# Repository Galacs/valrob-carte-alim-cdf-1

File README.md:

# Carte alim CDF 1

ESP32-S3-WROOM-1 5v 10A and 12v 10A six efuse protected with current and state monitoring channels power supply boards

The repo also contains minimal firmware for the ESP32 MCU.

## IC List

- ESP32-S3-WROOM-1 (Main MCU Module)
- TLV757P (MCU 3v3 LDO)
- 2X TPS56A37 (10A smps)
- SN65HVD (CAN transceiver)
- 7x TPS259472 (5A efuse)

## Top preview

## Preview 3d render

## Pictures

## Pin definitions

```c
#define PWR_STATUS_PIN 17

#define PG_12V_PIN 37
#define PG_5V_PIN 48
#define VSENSE_PIN 17

#define CAN_RX 35
#define CAN_TX 36

#define BAU 42

#define ILM_5V_1_PIN 1
#define ILM_5V_2_PIN 3
#define ILM_5V_3_PIN 2

#define ILM_12V_1_PIN 1
#define ILM_12V_2_PIN 7
#define ILM_12V_3_PIN 5
#define ILM_12V_4_PIN 4

#define EN_5V_1_PIN 39
#define EN_5V_2_PIN 21
#define EN_5V_3_PIN 40

#define EN_12V_1_PIN 11
#define EN_12V_2_PIN 13
#define EN_12V_3_PIN 8

#define PG_5V_1_PIN 38
#define PG_5V_2_PIN 47
#define PG_5V_3_PIN 41

#define PG_12V_1_PIN 10
#define PG_12V_2_PIN 12
#define PG_12V_3_PIN 18
#define PG_12V_4_PIN 16
```

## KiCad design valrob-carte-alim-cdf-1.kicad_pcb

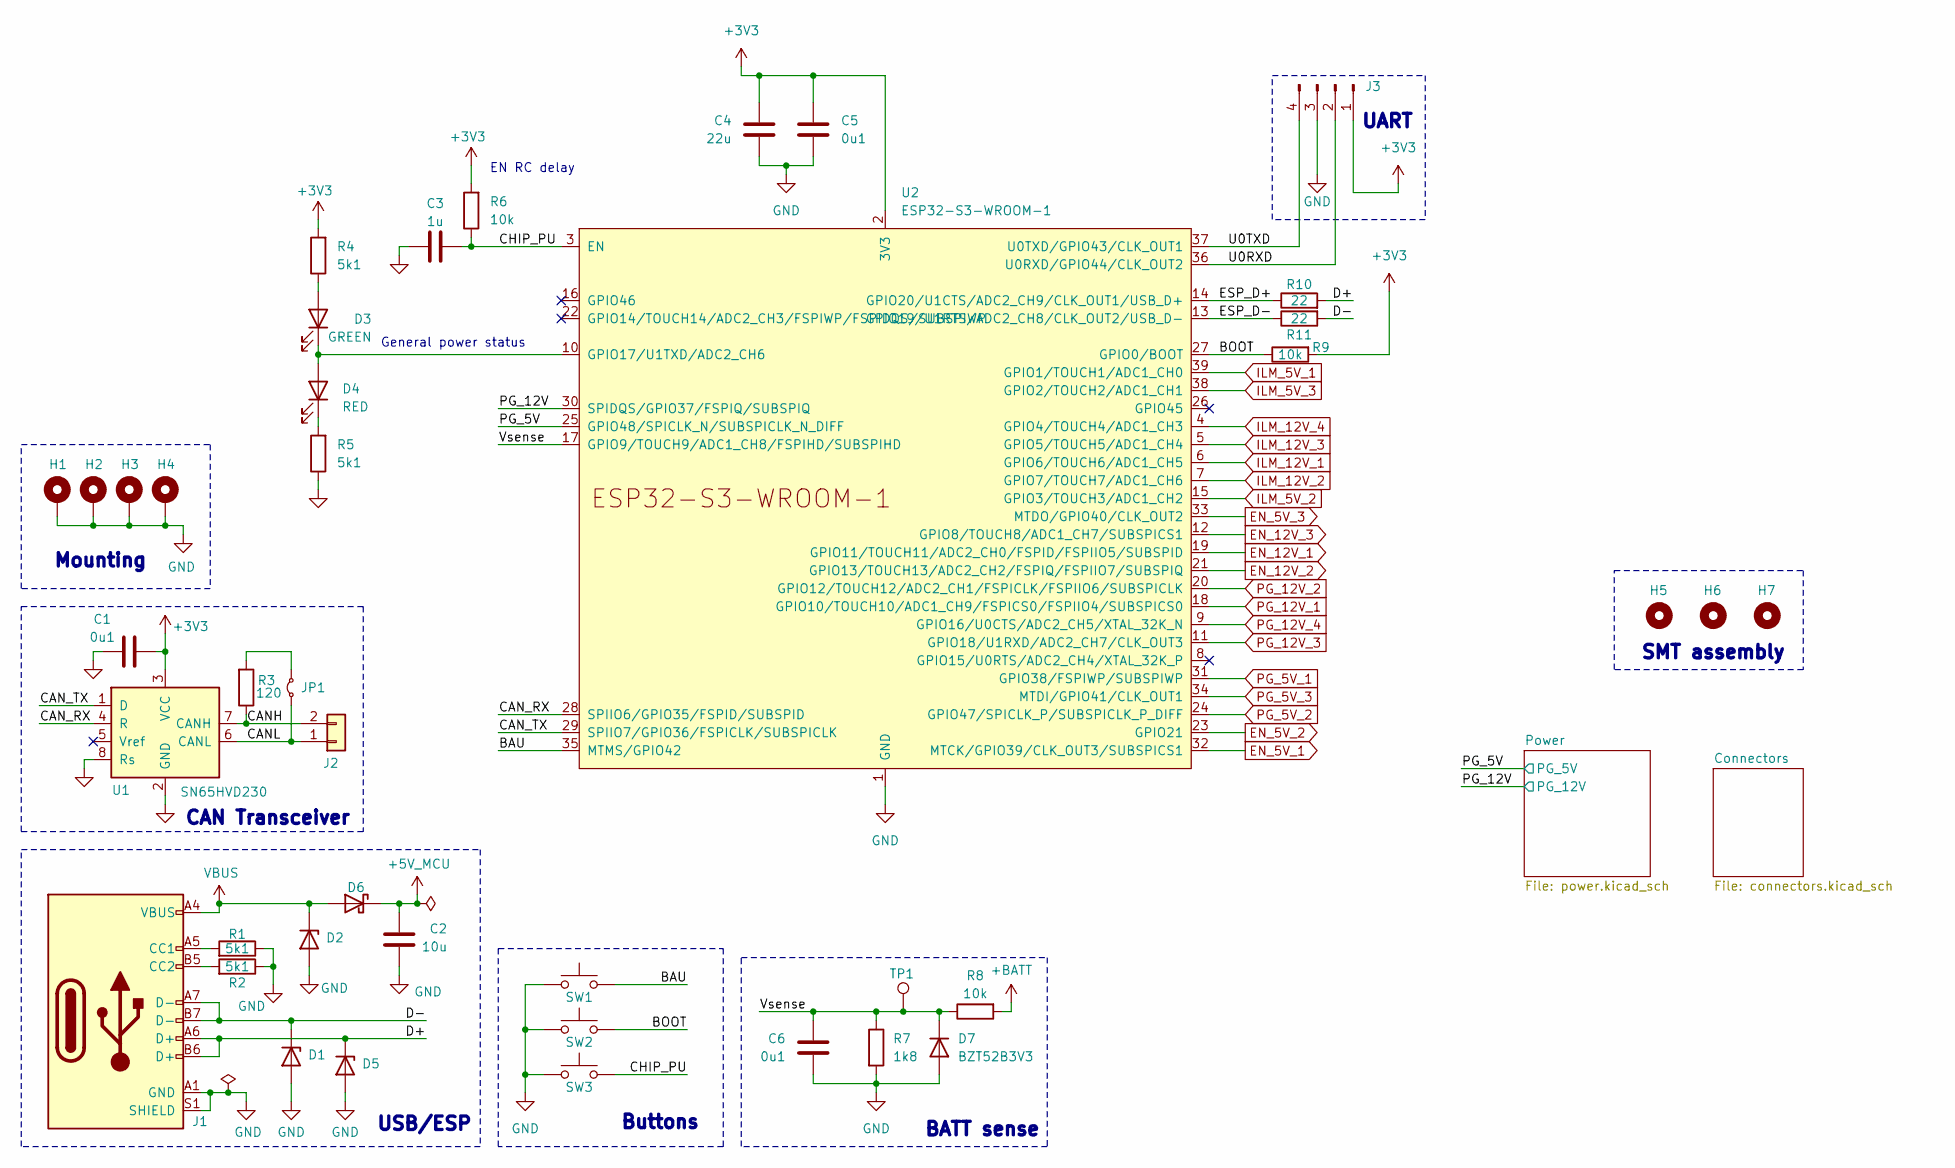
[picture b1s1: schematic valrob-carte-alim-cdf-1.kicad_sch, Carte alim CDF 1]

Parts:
C1, C5, C6: 0u1; C_0402_1005Metric; Manufacturer Part Number CL05B104KB54PNC; JLCPCB Part # C307331
C2: 10u; C_0603_1608Metric; Manufacturer Part Number CL10A106KP8NNNC; JLCPCB Part # C19702
C3: 1u; C_0402_1005Metric; Manufacturer Part Number CL05A105KA5NQNC; JLCPCB Part # C52923
C4: 22u; C_0603_1608Metric; Manufacturer Part Number CL10A226MQ8NRNC; JLCPCB Part # C59461
D1, D2, D5: H5VU10U; Diode_DFN1006; Manufacturer Part Number H5VU10U; JLCPCB Part # C22395519
D3: GREEN; LED_0805_2012Metric; Manufacturer Part Number KT-0805G; JLCPCB Part # C2297
D4: RED; LED_0603_1608Metric; Manufacturer Part Number KT-0603R; JLCPCB Part # C2286
D6: D_Schottky; D_SMA; Manufacturer Part Number SS54; JLCPCB Part # C22452
D7: BZT52B3V3; D_SOD-123; Manufacturer Part Number BZT52B3V3; JLCPCB Part # C19077392
H1, H2, H3, H4: MountingHole_Pad; MountingHole_2.2mm_M2_Pad_Via
H5, H6, H7: MountingHole; ToolingHole_1.152mm
J1: USB_C_Receptacle_USB2.0_14P; USB_C_Receptacle_HRO_TYPE-C-31-M-12; Manufacturer Part Number TYPE-C16PIN; JLCPCB Part # C393939
J2: Conn_01x02; JST_XH_B2B-XH-A_1x02_P2.50mm_Vertical; Manufacturer Part Number B2B-XH-A(LF)(SN); JLCPCB Part # C158012
J3: Conn_01x04_Pin; PinHeader_1x04_P2.54mm_Vertical
JP1: Jumper_2_Small_Bridged; SolderJumper-2_P1.3mm_Open_RoundedPad1.0x1.5mm
R1, R2, R4, R5: 5k1; R_0402_1005Metric; Manufacturer Part Number 0402WGF5101TCE; JLCPCB Part # C25905
R3: 120; R_1206_3216Metric; Manufacturer Part Number 1206W4F1200T5E; JLCPCB Part # C17909
R6, R8, R9: 10k; R_0402_1005Metric; Manufacturer Part Number 0402WGF1002TCE; JLCPCB Part # C25744
R7: 1k8; R_0603_1608Metric; Manufacturer Part Number 0603WAF1801T5E; JLCPCB Part # C4177
R10, R11: 22; R_0402_1005Metric; Manufacturer Part Number 0402WGF220JTCE; JLCPCB Part # C25092
SW1: SW_Push; JST_XH_B2B-XH-A_1x02_P2.50mm_Vertical; Manufacturer Part Number B2B-XH-A(LF)(SN); JLCPCB Part # C158012
SW2, SW3: SW_Push; SW_SPST_TS-1088-xR020; Manufacturer Part Number TS-1088-AR02016; JLCPCB Part # C720477
TP1: TestPoint; TestPoint_Pad_D2.0mm
U1: SN65HVD230; SOIC-8_3.9x4.9mm_P1.27mm; Manufacturer Part Number SN65HVD230DR; JLCPCB Part # C12084
U2: ESP32-S3-WROOM-1; Manufacturer Part Number ESP32-S3-WROOM-1-N8R2; JLCPCB Part # C2913204

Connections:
+3V3: C1.1, C4.1, C5.1, J3.1, R4.2, R6.2, R9.2, U1.3 (VCC), U2.2 (3V3); also elsewhere on the board
+5V_MCU: C2.1, D6.1 (K); also elsewhere on the board
+BATT: R8.2; also elsewhere on the board
/BAU: SW1.2, U2.35 (MTMS/GPIO42)
/BOOT: R9.1, SW2.2, U2.27 (GPIO0/BOOT)
/CANH: J2.2, R3.1, U1.7 (CANH)
/CANL: J2.1, JP1.1 (A), U1.6 (CANL)
/CAN_RX: U1.4 (R), U2.28 (SPIIO6/GPIO35/FSPID/SUBSPID)
/CAN_TX: U1.1 (D), U2.29 (SPIIO7/GPIO36/FSPICLK/SUBSPICLK)
/CHIP_PU: C3.2, R6.1, SW3.2, U2.3 (EN)
/D+: D5.1 (K), J1.A6 (D+), J1.B6 (D+), R10.2
/D-: D1.1 (K), J1.A7 (D-), J1.B7 (D-), R11.2
/ESP_D+: R10.1, U2.14 (GPIO20/U1CTS/ADC2_CH9/CLK_OUT1/USB_D+)
/ESP_D-: R11.1, U2.13 (GPIO19/U1RTS/ADC2_CH8/CLK_OUT2/USB_D-)
/PG_5V: U2.25 (GPIO48/SPICLK_N/SUBSPICLK_N_DIFF); also elsewhere on the board
/PG_12V: U2.30 (SPIDQS/GPIO37/FSPIQ/SUBSPIQ); also elsewhere on the board
/U0RXD: J3.2, U2.36 (U0RXD/GPIO44/CLK_OUT2)
/U0TXD: J3.4, U2.37 (U0TXD/GPIO43/CLK_OUT1)
/Vsense: C6.1, D7.1 (K), R7.1, R8.1, TP1.1, U2.17 (GPIO9/TOUCH9/ADC1_CH8/FSPIHD/SUBSPIHD)
EN_5V_1: U2.32 (MTCK/GPIO39/CLK_OUT3/SUBSPICS1); also elsewhere on the board
EN_5V_2: U2.23 (GPIO21); also elsewhere on the board
EN_5V_3: U2.33 (MTDO/GPIO40/CLK_OUT2); also elsewhere on the board
EN_12V_1: U2.19 (GPIO11/TOUCH11/ADC2_CH0/FSPID/FSPIIO5/S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); also elsewhere on the board
EN_12V_2: U2.21 (GPIO13/TOUCH13/ADC2_CH2/FSPIQ/FSPIIO7/S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); also elsewhere on the board
EN_12V_3: U2.12 (GPIO8/TOUCH8/ADC1_CH7/SUBSPICS1); also elsewhere on the board
GND: C1.2, C2.2, C3.1, C4.2, C5.2, C6.2, D1.2 (A), D2.2 (A), D5.2 (A), D7.2 (A), H1.1, H2.1, H3.1, H4.1, J1.A1 (GND), J1.A12 (GND), J1.B1 (GND), J1.B12 (GND), J1.S1 (SHIELD), J3.3, R1.1, R2.1, R5.1, R7.2, SW1.1, SW2.1, SW3.1, U1.2 (GND), U1.8 (Rs), U2.1 (GND), U2.40 (GND), U2.41 (GND); also elsewhere on the board
ILM_5V_1: U2.39 (GPIO1/TOUCH1/ADC1_CH0); also elsewhere on the board
ILM_5V_2: U2.15 (GPIO3/TOUCH3/ADC1_CH2); also elsewhere on the board
ILM_5V_3: U2.38 (GPIO2/TOUCH2/ADC1_CH1); also elsewhere on the board
ILM_12V_1: U2.6 (GPIO6/TOUCH6/ADC1_CH5); also elsewhere on the board
ILM_12V_2: U2.7 (GPIO7/TOUCH7/ADC1_CH6); also elsewhere on the board
ILM_12V_3: U2.5 (GPIO5/TOUCH5/ADC1_CH4); also elsewhere on the board
ILM_12V_4: U2.4 (GPIO4/TOUCH4/ADC1_CH3); also elsewhere on the board
unnamed: D3.2 (A), R4.1
unnamed: D3.1 (K), D4.2 (A), U2.10 (GPIO17/U1TXD/ADC2_CH6)
unnamed: D4.1 (K), R5.2
unnamed: J1.A5 (CC1), R1.2
unnamed: J1.B5 (CC2), R2.2
unnamed: JP1.2 (B), R3.2
PG_5V_1: U2.31 (GPIO38/FSPIWP/SUBSPIWP); also elsewhere on the board
PG_5V_2: U2.24 (GPIO47/SPICLK_P/SUBSPICLK_P_DIFF); also elsewhere on the board
PG_5V_3: U2.34 (MTDI/GPIO41/CLK_OUT1); also elsewhere on the board
PG_12V_1: U2.18 (GPIO10/TOUCH10/ADC1_CH9/FSPICS0/FSPIIO4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); also elsewhere on the board
PG_12V_2: U2.20 (GPIO12/TOUCH12/ADC2_CH1/FSPICLK/FSPIIO6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); also elsewhere on the board
PG_12V_3: U2.11 (GPIO18/U1RXD/ADC2_CH7/CLK_OUT3); also elsewhere on the board
PG_12V_4: U2.9 (GPIO16/U0CTS/ADC2_CH5/XTAL_32K_N); also elsewhere on the board
VBUS: D2.1 (K), D6.2 (A), J1.A4 (VBUS), J1.A9 (VBUS), J1.B4 (VBUS), J1.B9 (VBUS)

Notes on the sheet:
EN RC delay
Mounting
SMT assembly
UART
Buttons
USB/ESP
BATT sense
CAN Transceiver
General power status

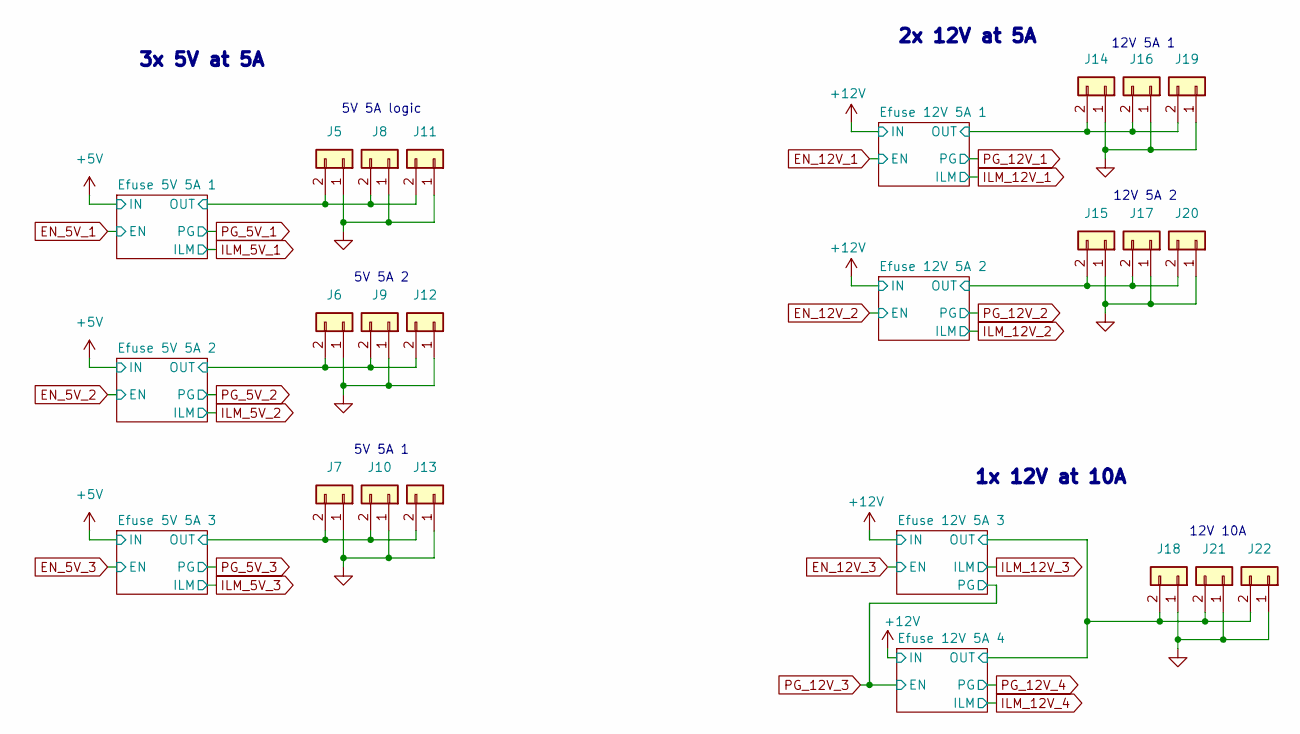
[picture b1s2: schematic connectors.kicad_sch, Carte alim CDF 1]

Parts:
J5, J6, J7, J8, J9, J10, J11, J12, J13, J14, J15, J16, J17, J18, J19, J20, J21, J22: Conn_01x02; JST_XH_B2B-XH-A_1x02_P2.50mm_Vertical; Manufacturer Part Number B2B-XH-A(LF)(SN); JLCPCB Part # C158012

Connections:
/Connectors/Efuse 5V 5A 1/OUT: J5.2, J8.2, J11.2; also elsewhere on the board
/Connectors/Efuse 5V 5A 2/OUT: J6.2, J9.2, J12.2; also elsewhere on the board
/Connectors/Efuse 5V 5A 3/OUT: J7.2, J10.2, J13.2; also elsewhere on the board
/Connectors/Efuse 12V 5A 1/OUT: J14.2, J16.2, J19.2; also elsewhere on the board
/Connectors/Efuse 12V 5A 2/OUT: J15.2, J17.2, J20.2; also elsewhere on the board
/Connectors/Efuse 12V 5A 3/OUT: J18.2, J21.2, J22.2; also elsewhere on the board
GND: J5.1, J6.1, J7.1, J8.1, J9.1, J10.1, J11.1, J12.1, J13.1, J14.1, J15.1, J16.1, J17.1, J18.1, J19.1, J20.1, J21.1, J22.1; also elsewhere on the board

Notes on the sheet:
5V 5A 1
12V 5A 2
12V 5A 1
2x 12V at 5A
1x 12V at 10A
12V 10A
5V 5A 2
3x 5V at 5A
5V 5A logic

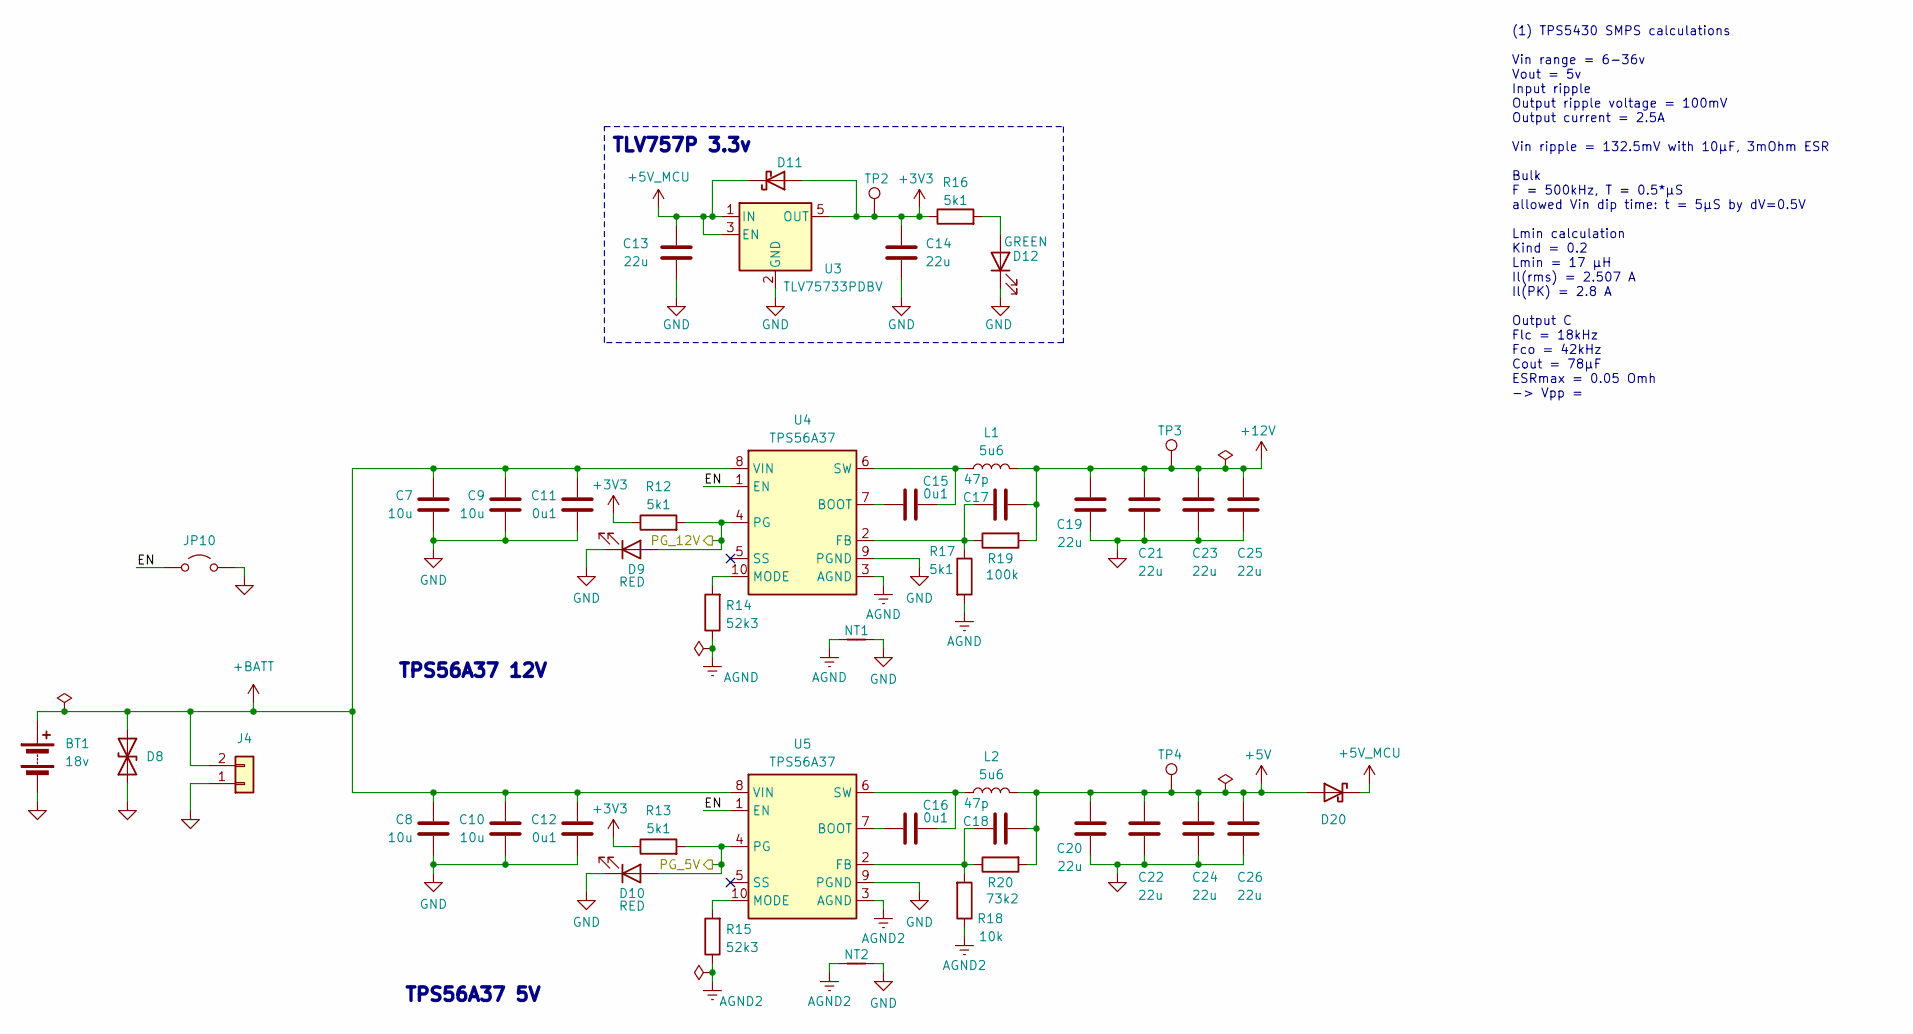
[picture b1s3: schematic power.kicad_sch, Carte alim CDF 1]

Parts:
BT1: 18v; Power battery holder
C7, C8, C9, C10: 10u; C_0805_2012Metric; Manufacturer Part Number GRM21BR61H106KE43L; JLCPCB Part # C440198
C11, C12, C15, C16: 0u1; C_0402_1005Metric; Manufacturer Part Number CL05B104KB54PNC; JLCPCB Part # C307331
C13, C14: 22u; C_0603_1608Metric; Manufacturer Part Number CL10A226MQ8NRNC; JLCPCB Part # C59461
C17, C18: 47p; C_0402_1005Metric; Manufacturer Part Number 0402CG470J500NT; JLCPCB Part # C1567
C19, C20, C21, C22, C23, C24, C25, C26: 22u; C_0805_2012Metric; Manufacturer Part Number CL21A226MAQNNNE; JLCPCB Part # C45783
D8: D_TVS; D_SMA; Manufacturer Part Number SMAJ33CA; JLCPCB Part # C19077549
D9, D10: RED; LED_0603_1608Metric; Manufacturer Part Number KT-0603R; JLCPCB Part # C2286
D11, D20: D_Schottky; D_SMA; Manufacturer Part Number SS54; JLCPCB Part # C22452
D12: GREEN; LED_0805_2012Metric; Manufacturer Part Number KT-0805G; JLCPCB Part # C2297
J4: Conn_01x02; JST_XH_B2B-XH-A_1x02_P2.50mm_Vertical; Manufacturer Part Number B2B-XH-A(LF)(SN); JLCPCB Part # C158012
JP10: Jumper_2_Small_Open; PinHeader_2x01_P2.54mm_Vertical
L1, L2: 5u6; L_Bourns_SRP1050WA; Manufacturer Part Number SMMS1050-5R6M; JLCPCB Part # C149541
NT1, NT2: NetTie_2; NetTie-2_SMD_Pad0.5mm
R12, R13, R16, R17: 5k1; R_0402_1005Metric; Manufacturer Part Number 0402WGF5101TCE; JLCPCB Part # C25905
R14, R15: 52k3; R_0402_1005Metric; Manufacturer Part Number 0402WGF5232TCE; JLCPCB Part # C26982
R18: 10k; R_0402_1005Metric; Manufacturer Part Number 0402WGF1002TCE; JLCPCB Part # C25744
R19: 100k; R_0402_1005Metric; Manufacturer Part Number 0402WGF1003TCE; JLCPCB Part # C25741
R20: 73k2; R_0402_1005Metric; Manufacturer Part Number 0402WGF7322TCE; JLCPCB Part # C26986
TP2, TP3, TP4: TestPoint; TestPoint_Pad_D2.0mm
U3: TLV75733PDBV; SOT-23-5; Manufacturer Part Number TLV75733PDBVR; JLCPCB Part # C485517
U4, U5: TPS56A37; Texas_RPA0010A_VQFN-HR-10_3x3mm_P0.5mm; Manufacturer Part Number TPS56A37RPAR; JLCPCB Part # C22392669

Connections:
+3V3: C14.2, D11.2 (A), R12.1, R13.1, R16.1, TP2.1, U3.5 (OUT); also elsewhere on the board
+5V: C18.2, C20.1, C22.1, C24.1, C26.1, D20.2 (A), L2.2, R20.2, TP4.1; also elsewhere on the board
+5V_MCU: C13.2, D11.1 (K), D20.1 (K), U3.1 (IN), U3.3 (EN); also elsewhere on the board
+12V: C17.2, C19.1, C21.1, C23.1, C25.1, L1.2, R19.2, TP3.1; also elsewhere on the board
+BATT: BT1.1 (+), C7.1, C8.1, C9.1, C10.1, C11.1, C12.1, D8.2 (A2), J4.2, U4.8 (VIN), U5.8 (VIN); also elsewhere on the board
/PG_5V: D10.2 (A), R13.2, U5.4 (PG); also elsewhere on the board
/PG_12V: D9.2 (A), R12.2, U4.4 (PG); also elsewhere on the board
/Power/EN: JP10.1 (A), U4.1 (EN), U5.1 (EN)
AGND: NT1.1, R14.1, R17.2, U4.3 (AGND)
AGND2: NT2.1, R15.1, R18.1, U5.3 (AGND)
GND: BT1.2 (-), C7.2, C8.2, C9.2, C10.2, C11.2, C12.2, C13.1, C14.1, C19.2, C20.2, C21.2, C22.2, C23.2, C24.2, C25.2, C26.2, D8.1 (A1), D9.1 (K), D10.1 (K), D12.1 (K), J4.1, JP10.2 (B), NT1.2, NT2.2, U3.2 (GND), U4.9 (PGND), U5.9 (PGND); also elsewhere on the board
unnamed: D12.2 (A), R16.2
unnamed: C15.1, U4.7 (BOOT)
unnamed: C17.1, R17.1, R19.1, U4.2 (FB)
unnamed: R14.2, U4.10 (MODE)
unnamed: C15.2, L1.1, U4.6 (SW)
unnamed: C16.1, U5.7 (BOOT)
unnamed: C18.1, R18.2, R20.1, U5.2 (FB)
unnamed: R15.2, U5.10 (MODE)
unnamed: C16.2, L2.1, U5.6 (SW)

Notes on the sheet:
TPS56A37 12V
TLV757P 3.3v
TPS56A37 5V
(1) TPS5430 SMPS calculations Vin range = 6-36v Vout = 5v Input ripple Output ripple voltage = 100mV Output current = 2.5A Vin ripple = 132.5mV with 10µF, 3mOhm ESR Bulk F = 500kHz, T = 0.5*µS allowed Vin dip time: t = 5µS by dV=0.5V Lmin calculation Kind = 0.2 Lmin = 17 µH Il(rms) = 2.507 A Il(PK)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

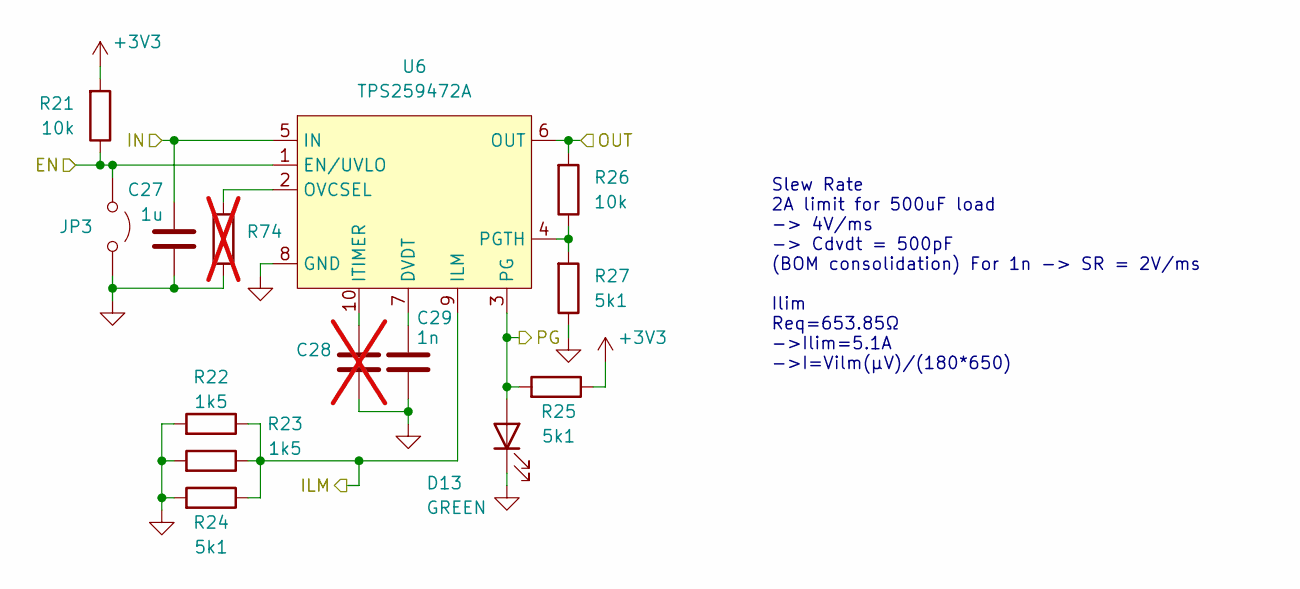
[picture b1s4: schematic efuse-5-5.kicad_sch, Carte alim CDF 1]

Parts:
C27: 1u; C_0402_1005Metric; Manufacturer Part Number CL05A105KA5NQNC; JLCPCB Part # C52923
C28: C; C_0402_1005Metric; not fitted
C29: 1n; C_0402_1005Metric; Manufacturer Part Number 0402B102K500NT; JLCPCB Part # C1523
D13: GREEN; LED_0805_2012Metric; Manufacturer Part Number KT-0805G; JLCPCB Part # C2297
JP3: Jumper_2_Small_Open; PinHeader_2x01_P2.54mm_Vertical
R21, R26: 10k; R_0402_1005Metric; Manufacturer Part Number 0402WGF1002TCE; JLCPCB Part # C25744
R22, R23: 1k5; R_0402_1005Metric; Manufacturer Part Number 0402WGF1501TCE; JLCPCB Part # C25867
R24, R25, R27: 5k1; R_0402_1005Metric; Manufacturer Part Number 0402WGF5101TCE; JLCPCB Part # C25905
R74: R; R_0402_1005Metric; not fitted
U6: TPS259472A; Texas_RPW0010A_VQFN-HR-10_2x2mm_P0.5mm; Manufacturer Part Number TPS259472ARPWR; JLCPCB Part # C3662789

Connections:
+3V3: R21.2, R25.1; also elsewhere on the board
+5V: C27.2, U6.5 (IN); also elsewhere on the board
/Connectors/Efuse 5V 5A 1/OUT: R26.2, U6.6 (OUT); also elsewhere on the board
EN_5V_1: JP3.1 (A), R21.1, U6.1 (EN/UVLO); also elsewhere on the board
GND: C27.1, C28.2, C29.2, D13.1 (K), JP3.2 (B), R22.2, R23.2, R24.2, R27.1, R74.2, U6.8 (GND); also elsewhere on the board
ILM_5V_1: R22.1, R23.1, R24.1, U6.9 (ILM); also elsewhere on the board
unnamed: C29.1, U6.7 (DVDT)
unnamed: C28.1, U6.10 (ITIMER)
unnamed: R74.1, U6.2 (OVCSEL)
unnamed: R26.1, R27.2, U6.4 (PGTH)
PG_5V_1: D13.2 (A), R25.2, U6.3 (PG); also elsewhere on the board

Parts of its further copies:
C30, C45: 1u; C_0402_1005Metric; Manufacturer Part Number CL05A105KA5NQNC; JLCPCB Part # C52923
C31, C46: C; C_0402_1005Metric; not fitted
C32, C47: 1n; C_0402_1005Metric; Manufacturer Part Number 0402B102K500NT; JLCPCB Part # C1523
D14, D19: GREEN; LED_0805_2012Metric; Manufacturer Part Number KT-0805G; JLCPCB Part # C2297
JP4, JP9: Jumper_2_Small_Open; PinHeader_2x01_P2.54mm_Vertical
R28, R33, R67, R72: 10k; R_0402_1005Metric; Manufacturer Part Number 0402WGF1002TCE; JLCPCB Part # C25744
R29, R30, R68, R69: 1k5; R_0402_1005Metric; Manufacturer Part Number 0402WGF1501TCE; JLCPCB Part # C25867
R31, R32, R34, R70, R71, R73: 5k1; R_0402_1005Metric; Manufacturer Part Number 0402WGF5101TCE; JLCPCB Part # C25905
R75, R76: R; R_0402_1005Metric; not fitted
U7, U12: TPS259472A; Texas_RPW0010A_VQFN-HR-10_2x2mm_P0.5mm; Manufacturer Part Number TPS259472ARPWR; JLCPCB Part # C3662789

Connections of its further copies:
+3V3: R28.2, R32.1, R67.2, R71.1; also elsewhere on the board
+5V: C30.2, C45.2, U7.5 (IN), U12.5 (IN); also elsewhere on the board
/Connectors/Efuse 5V 5A 2/OUT: R72.2, U12.6 (OUT); also elsewhere on the board
/Connectors/Efuse 5V 5A 3/OUT: R33.2, U7.6 (OUT); also elsewhere on the board
EN_5V_2: JP9.1 (A), R67.1, U12.1 (EN/UVLO); also elsewhere on the board
EN_5V_3: JP4.1 (A), R28.1, U7.1 (EN/UVLO); also elsewhere on the board
GND: C30.1, C31.2, C32.2, C45.1, C46.2, C47.2, D14.1 (K), D19.1 (K), JP4.2 (B), JP9.2 (B), R29.2, R30.2, R31.2, R34.1, R68.2, R69.2, R70.2, R73.1, R75.2, R76.2, U7.8 (GND), U12.8 (GND); also elsewhere on the board
ILM_5V_2: R68.1, R69.1, R70.1, U12.9 (ILM); also elsewhere on the board
ILM_5V_3: R29.1, R30.1, R31.1, U7.9 (ILM); also elsewhere on the board
unnamed: C32.1, U7.7 (DVDT)
unnamed: C31.1, U7.10 (ITIMER)
unnamed: R75.1, U7.2 (OVCSEL)
unnamed: R33.1, R34.2, U7.4 (PGTH)
unnamed: C47.1, U12.7 (DVDT)
unnamed: C46.1, U12.10 (ITIMER)
unnamed: R76.1, U12.2 (OVCSEL)
unnamed: R72.1, R73.2, U12.4 (PGTH)
PG_5V_2: D19.2 (A), R71.2, U12.3 (PG); also elsewhere on the board
PG_5V_3: D14.2 (A), R32.2, U7.3 (PG); also elsewhere on the board

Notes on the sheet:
Slew Rate 2A limit for 500uF load -> 4V/ms -> Cdvdt = 500pF (BOM consolidation) For 1n -> SR = 2V/ms Ilim Req=653.85Ω ->Ilim=5.1A ->I=Vilm(µV)/(180*650)

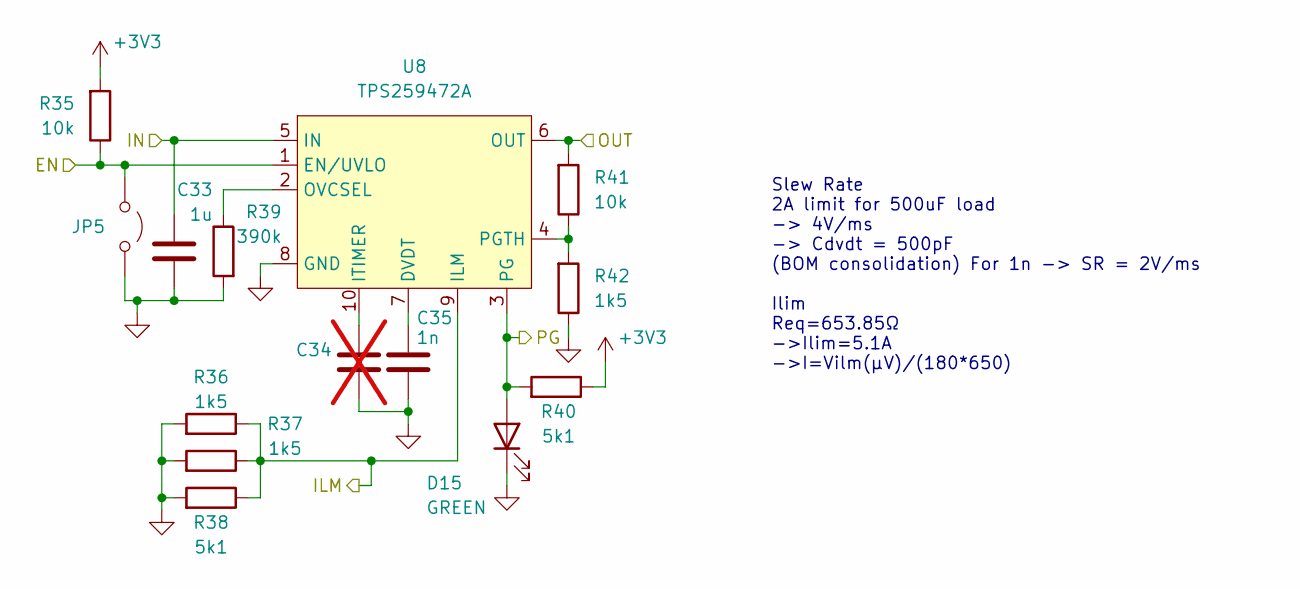
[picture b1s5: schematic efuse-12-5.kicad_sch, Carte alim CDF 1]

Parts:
C33: 1u; C_0402_1005Metric; Manufacturer Part Number CL05A105KA5NQNC; JLCPCB Part # C52923
C34: C; C_0402_1005Metric; not fitted
C35: 1n; C_0402_1005Metric; Manufacturer Part Number 0402B102K500NT; JLCPCB Part # C1523
D15: GREEN; LED_0805_2012Metric; Manufacturer Part Number KT-0805G; JLCPCB Part # C2297
JP5: Jumper_2_Small_Open; PinHeader_2x01_P2.54mm_Vertical
R35, R41: 10k; R_0402_1005Metric; Manufacturer Part Number 0402WGF1002TCE; JLCPCB Part # C25744
R36, R37, R42: 1k5; R_0402_1005Metric; Manufacturer Part Number 0402WGF1501TCE; JLCPCB Part # C25867
R38, R40: 5k1; R_0402_1005Metric; Manufacturer Part Number 0402WGF5101TCE; JLCPCB Part # C25905
R39: 390k; R_0402_1005Metric; Manufacturer Part Number 0402WGF3903TCE; JLCPCB Part # C25782
U8: TPS259472A; Texas_RPW0010A_VQFN-HR-10_2x2mm_P0.5mm; Manufacturer Part Number TPS259472ARPWR; JLCPCB Part # C3662789

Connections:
+3V3: R35.2, R40.1; also elsewhere on the board
+12V: C33.2, U8.5 (IN); also elsewhere on the board
/Connectors/Efuse 12V 5A 1/OUT: R41.2, U8.6 (OUT); also elsewhere on the board
EN_12V_1: JP5.1 (A), R35.1, U8.1 (EN/UVLO); also elsewhere on the board
GND: C33.1, C34.2, C35.2, D15.1 (K), JP5.2 (B), R36.2, R37.2, R38.2, R39.2, R42.1, U8.8 (GND); also elsewhere on the board
ILM_12V_1: R36.1, R37.1, R38.1, U8.9 (ILM); also elsewhere on the board
unnamed: C35.1, U8.7 (DVDT)
unnamed: C34.1, U8.10 (ITIMER)
unnamed: R39.1, U8.2 (OVCSEL)
unnamed: R41.1, R42.2, U8.4 (PGTH)
PG_12V_1: D15.2 (A), R40.2, U8.3 (PG); also elsewhere on the board

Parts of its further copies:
C36, C39, C42: 1u; C_0402_1005Metric; Manufacturer Part Number CL05A105KA5NQNC; JLCPCB Part # C52923
C37, C40, C43: C; C_0402_1005Metric; not fitted
C38, C41, C44: 1n; C_0402_1005Metric; Manufacturer Part Number 0402B102K500NT; JLCPCB Part # C1523
D16, D17, D18: GREEN; LED_0805_2012Metric; Manufacturer Part Number KT-0805G; JLCPCB Part # C2297
JP6, JP7, JP8: Jumper_2_Small_Open; PinHeader_2x01_P2.54mm_Vertical
R43, R49, R51, R57, R59, R65: 10k; R_0402_1005Metric; Manufacturer Part Number 0402WGF1002TCE; JLCPCB Part # C25744
R44, R45, R50, R52, R53, R58, R60, R61, R66: 1k5; R_0402_1005Metric; Manufacturer Part Number 0402WGF1501TCE; JLCPCB Part # C25867
R46, R48, R54, R56, R62, R64: 5k1; R_0402_1005Metric; Manufacturer Part Number 0402WGF5101TCE; JLCPCB Part # C25905
R47, R55, R63: 390k; R_0402_1005Metric; Manufacturer Part Number 0402WGF3903TCE; JLCPCB Part # C25782
U9, U10, U11: TPS259472A; Texas_RPW0010A_VQFN-HR-10_2x2mm_P0.5mm; Manufacturer Part Number TPS259472ARPWR; JLCPCB Part # C3662789

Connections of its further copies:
+3V3: R43.2, R48.1, R51.2, R56.1, R59.2, R64.1; also elsewhere on the board
+12V: C36.2, C39.2, C42.2, U9.5 (IN), U10.5 (IN), U11.5 (IN); also elsewhere on the board
/Connectors/Efuse 12V 5A 2/OUT: R49.2, U9.6 (OUT); also elsewhere on the board
/Connectors/Efuse 12V 5A 3/OUT: R57.2, R65.2, U10.6 (OUT), U11.6 (OUT); also elsewhere on the board
EN_12V_2: JP6.1 (A), R43.1, U9.1 (EN/UVLO); also elsewhere on the board
EN_12V_3: JP7.1 (A), R51.1, U10.1 (EN/UVLO); also elsewhere on the board
GND: C36.1, C37.2, C38.2, C39.1, C40.2, C41.2, C42.1, C43.2, C44.2, D16.1 (K), D17.1 (K), D18.1 (K), JP6.2 (B), JP7.2 (B), JP8.2 (B), R44.2, R45.2, R46.2, R47.2, R50.1, R52.2, R53.2, R54.2, R55.2, R58.1, R60.2, R61.2, R62.2, R63.2, R66.1, U9.8 (GND), U10.8 (GND), U11.8 (GND); also elsewhere on the board
ILM_12V_2: R44.1, R45.1, R46.1, U9.9 (ILM); also elsewhere on the board
ILM_12V_3: R52.1, R53.1, R54.1, U10.9 (ILM); also elsewhere on the board
ILM_12V_4: R60.1, R61.1, R62.1, U11.9 (ILM); also elsewhere on the board
unnamed: C38.1, U9.7 (DVDT)
unnamed: C37.1, U9.10 (ITIMER)
unnamed: R47.1, U9.2 (OVCSEL)
unnamed: R49.1, R50.2, U9.4 (PGTH)
unnamed: C41.1, U10.7 (DVDT)
unnamed: C40.1, U10.10 (ITIMER)
unnamed: R55.1, U10.2 (OVCSEL)
unnamed: R57.1, R58.2, U10.4 (PGTH)
unnamed: C44.1, U11.7 (DVDT)
unnamed: C43.1, U11.10 (ITIMER)
unnamed: R63.1, U11.2 (OVCSEL)
unnamed: R65.1, R66.2, U11.4 (PGTH)
PG_12V_2: D16.2 (A), R48.2, U9.3 (PG); also elsewhere on the board
PG_12V_3: D17.2 (A), JP8.1 (A), R56.2, R59.1, U10.3 (PG), U11.1 (EN/UVLO); also elsewhere on the board
PG_12V_4: D18.2 (A), R64.2, U11.3 (PG); also elsewhere on the board

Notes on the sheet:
Slew Rate 2A limit for 500uF load -> 4V/ms -> Cdvdt = 500pF (BOM consolidation) For 1n -> SR = 2V/ms Ilim Req=653.85Ω ->Ilim=5.1A ->I=Vilm(µV)/(180*650)

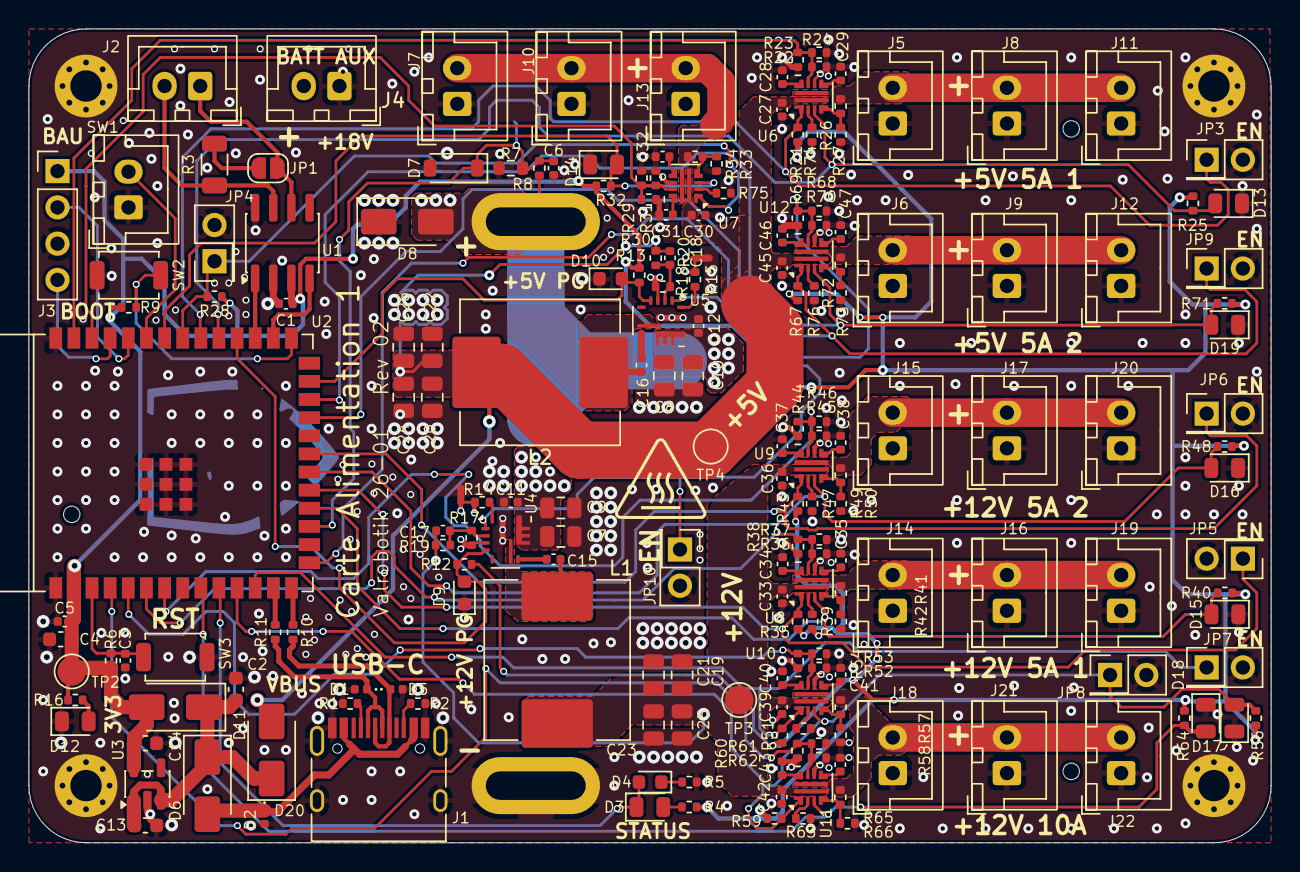
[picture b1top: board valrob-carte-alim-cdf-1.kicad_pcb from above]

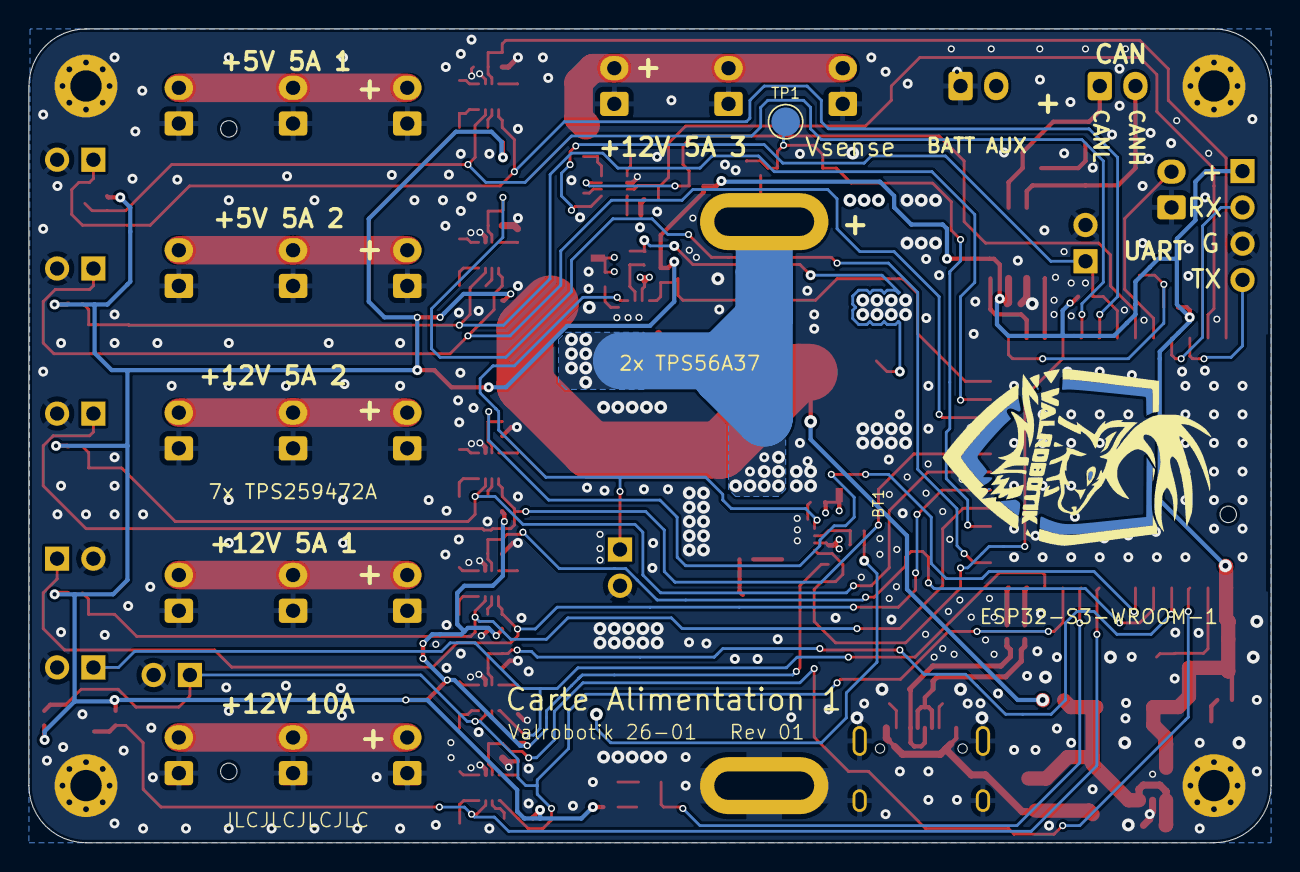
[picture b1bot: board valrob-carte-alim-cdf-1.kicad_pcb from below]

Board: 4 copper layers, 87.0 x 57.0 mm, 205 parts (2 on the bottom side), 95 nets.

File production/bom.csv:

Designator,Footprint,Quantity,Value,LCSC Part #
BT1,Power battery holder,1,18v,
"C1, C11, C12, C15, C16, C5, C6",0402,7,0u1,C307331
"C10, C7, C8, C9",0805,4,10u,C440198
"C13, C14, C4",0603,3,22u,C59461
"C17, C18",0402,2,47p,C1567
"C19, C20, C21, C22, C23, C24, C25, C26",0805,8,22u,C45783
C2,0603,1,10u,C19702
"C27, C3, C30, C33, C36, C39, C42, C45",0402,8,1u,C52923
"C29, C32, C35, C38, C41, C44, C47",0402,7,1n,C1523
"D1, D2, D5",Diode_DFN1006,3,H5VU10U,C22395519
"D10, D4, D9",0603,3,RED,C2286
"D11, D20, D6",D_SMA,3,D_Schottky,C22452
"D12, D13, D14, D15, D16, D17, D18, D19, D3",0805,9,GREEN,C2297
D7,D_SOD-123,1,BZT52B3V3,C19077392
D8,D_SMA,1,D_TVS,C19077549
J1,USB_C_Receptacle_HRO_TYPE-C-31-M-12,1,USB_C_Receptacle_USB2.0_14P,C393939
"J10, J11, J12, J13, J14, J15, J16, J17, J18, J19, J2, J20, J21, J22, J4, J5, J6, J7, J8, J9",JST_XH_B2B-XH-A_1x02_P2.50mm_Vertical,20,Conn_01x02,C158012
"JP10, JP3, JP4, JP5, JP6, JP7, JP8, JP9",PinHeader_2x01_P2.54mm_Vertical,8,Jumper_2_Small_Open,
"L1, L2",L_Bourns_SRP1050WA,2,5u6,C149541
"R1, R12, R13, R16, R17, R2, R24, R25, R27, R31, R32, R34, R38, R4, R40, R46, R48, R5, R54, R56, R62, R64, R70, R71, R73",0402,25,5k1,C25905
"R10, R11",0402,2,22,C25092
"R14, R15",0402,2,52k3,C26982
"R18, R21, R26, R28, R33, R35, R41, R43, R49, R51, R57, R59, R6, R65, R67, R72, R8, R9",0402,18,10k,C25744
R19,0402,1,100k,C25741
R20,0402,1,73k2,C26986
"R22, R23, R29, R30, R36, R37, R42, R44, R45, R50, R52, R53, R58, R60, R61, R66, R68, R69",0402,18,1k5,C25867
R3,1206,1,120,C17909
"R39, R47, R55, R63",0402,4,390k,C25782
R7,0603,1,1k8,C4177
SW1,JST_XH_B2B-XH-A_1x02_P2.50mm_Vertical,1,SW_Push,C158012
"SW2, SW3",SW_SPST_TS-1088-xR020,2,SW_Push,C720477
U1,SOIC-8_3.9x4.9mm_P1.27mm,1,SN65HVD230,C12084
"U10, U11, U12, U6, U7, U8, U9",Texas_RPW0010A_VQFN-HR-10_2x2mm_P0.5mm,7,TPS259472A,C3662789
U3,SOT-23-5,1,TLV75733PDBV,C485517
"U4, U5",Texas_RPA0010A_VQFN-HR-10_3x3mm_P0.5mm,2,TPS56A37,C22392669

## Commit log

2026-01-14 schem: add ESP32-S3-WROOM-1 MCU
2026-01-14 schem: add USBC connector
2026-01-14 schem: add TPS5430 5v logic SMPS
2026-01-14 schem: moved TSP5430 to power sheet
2026-01-14 schem: add efuse page
2026-01-14 schem: add BOOT and CHIP_PU btns
2026-01-14 schem: add TPS259472A efuse
2026-01-14 schem: add TPS56A37 12V SMPS
2026-01-14 schem: add TPS56A37 5V SMPS
2026-01-14 schem: add battery esd tvs diode
2026-01-14 schem: add TPS259472A 5V 5A efuse
2026-01-14 schem: add VBUS TO +5V jumper
2026-01-14 schem: add 2 5V rails
2026-01-14 schem: add 2 12V 5A rails
2026-01-14 schem: add ILM pins and 12V 10A rail
2026-01-14 schem: add TLV757P 3.3v LDO
2026-01-14 schem: reorganize connectors
2026-01-14 schem: add +BATT voltage sense
2026-01-14 schem: add CAN transceiver
2026-01-14 schem: add additional connector for batt vin
2026-01-14 schem: update 12v efuse net labels
2026-01-14 schem: add BAU
2026-01-14 schem: update 12V efuse component class
2026-01-15 schem: remove logic 5V smps
2026-01-15 schem: removed 5V output
2026-01-15 schem: add disable jumper to efuses
2026-01-15 schem: add esp32 gpio connections
2026-01-15 schem: add general power status leds
2026-01-15 schem: change aux batt power connector
2026-01-15 schem: add test points
2026-01-15 schem: run and fix ERC
2026-01-15 schem: add net classes
2026-01-15 schem: add battery holder footprint
2026-01-15 schem: update TPS259472A symbol
2026-01-15 schem: complete BOM
2026-01-15 schem: add sheet title
2026-01-15 schem: renumber
2026-01-15 pcb: import stackup and constraints
2026-01-15 pcb: import footprints from schema
2026-01-15 pcb: add missing 3D models
2026-01-15 pcb: add initial rough layout
2026-01-15 pcb: add battery step file
2026-01-16 schem: add mounting holes
2026-01-16 pcb: refine layout
2026-01-16 pcb: add smps layout
2026-01-16 pcb: add efuse layout
2026-01-16 pcb: finish initial layout
2026-01-16 pcb: line up 2.54 headers
2026-01-16 pcb: add can layout
2026-01-16 pcb: add gnd planes
2026-01-16 pcb: add grid/place origin
2026-01-16 pcb: add gnd vias
2026-01-16 pcb: add high I 12V and 5V pwr routing
2026-01-16 pcb: add 5V SMPS routing
2026-01-16 pcb: fix 12v copper pour appearance
2026-01-16 pcb: add 12V SMPS routing
2026-01-16 pcb: add usb routing
2026-01-16 pcb: add can routing
2026-01-16 pcb: complete smps routing
2026-01-16 pcb: add efuse 5v 3 routing
2026-01-16 pcb: add esp and ldo 3v3 routing
2026-01-16 schem: reorganize programmable gpios
2026-01-17 pcb: increase size of negative batt spokes
2026-01-17 pcb: add local efuse routing
2026-01-17 pcb: add CHIP_PU routing
2026-01-17 pcb: add efuses' PG leds and en jumpers routing
2026-01-17 pcb: add BAU routing
2026-01-17 schem: add general EN jumper
2026-01-17 pcb: add efuses' PG AND EN routing
2026-01-17 pcb: add vsense routing
2026-01-17 pcb: add efuses ILM routing
2026-01-17 pcb: add 5V SMPS PG routing
2026-01-17 pcb: add BOOT routing
2026-01-17 pcb: add missing efuse EN routing to MCU
2026-01-17 pcb: add 3V3 pwr routing
2026-01-17 pcb: run and fix DRC
2026-01-17 pcb: add stitching vias
2026-01-17 pcb: remove unused internal pads
2026-01-17 pcb(silkscreen): clean reference designators
2026-01-17 pcb: add title and logo
2026-01-17 pcb(silkscreen): add user txt
2026-01-17 pcb: add title
2026-01-21 schem/pcb: put vsense on adc input
2026-01-21 pcb: add production files
2026-01-21 schem/pcb: prevent TPS56A37 reverse current with new oringed 5v mcu rail
2026-01-21 pcb: switch smps power capacitors zone connection to solid
2026-01-21 regenerate production files
2026-01-21 pcb: clean silkscreen and regenerate production files
2026-02-08 fw: initial commit
2026-02-08 fw: add pins definitions
2026-02-08 fw: add power channel object
2026-02-08 fw: update platformio.ini
2026-02-08 fw: add power channel impl
2026-02-08 fw: add pwr led update fn
2026-02-08 fw: add ems update fn
2026-02-08 fw: fix channels ems states
2026-02-08 fw: add current monitoring
2026-02-08 fw: add remaining channels to code
2026-02-09 fw: add commander lib
2026-02-09 fw: add commander serial interface
2026-02-09 fw: fix linking issue
2026-02-10 add README.md
2026-02-10 docs: add pictures to README
2026-02-10 docs: add additional picture to README
2026-02-21 schem/pcb: update batt connector and efuses footprints
2026-02-21 schem/pcb: update pwr inductors footprint and MPN
2026-02-21 rev 02
2026-02-21 pcb: add jlc tooling holes
2026-05-10 change to pioarduino esp32 platform
2026-05-10 disable +5v 2 on ems
2026-05-10 add 150ms PG debounce delay
